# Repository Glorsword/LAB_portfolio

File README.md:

# LAB_portfolio
Here you would find sample projects from our team

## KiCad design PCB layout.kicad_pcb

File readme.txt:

This project is quite simple, and it was the start for our team, it almost had no challenges other than finding a suitable Battery, but I chose an unrealistic unpractical huge battery.
other than that I put this project just to rember our humble beginnings

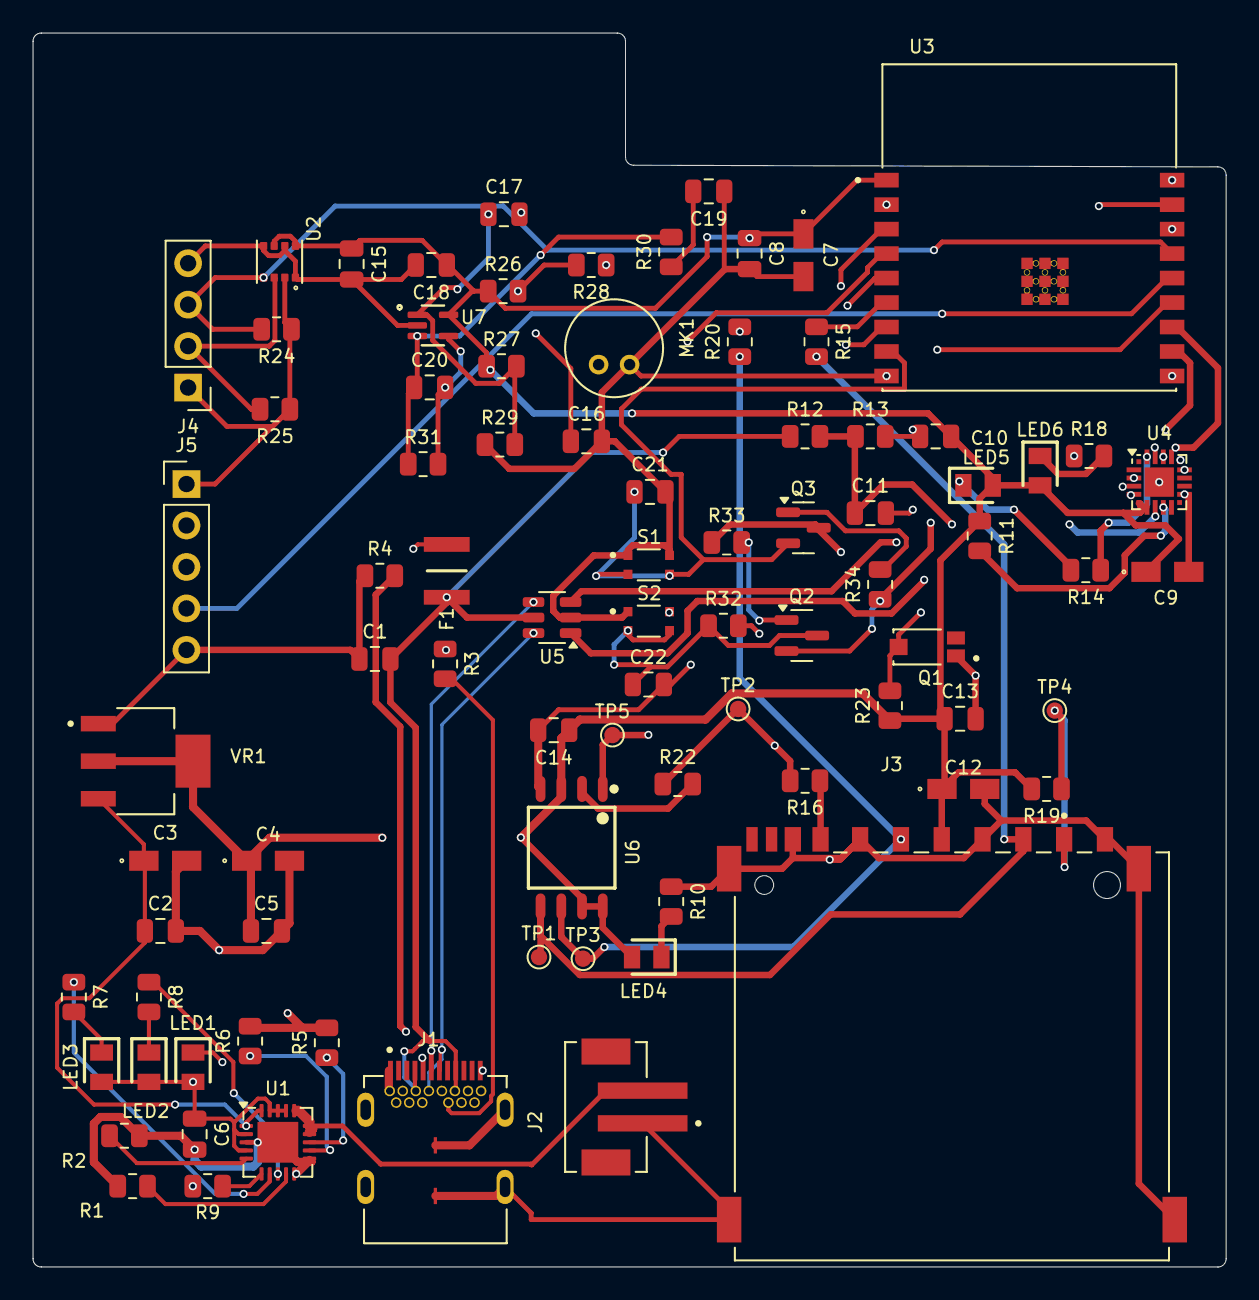
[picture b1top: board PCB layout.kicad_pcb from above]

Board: 4 copper layers, 73.1 x 75.6 mm, 85 parts (0 on the bottom side), 59 nets.

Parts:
C1, C2, C5, C8, C10, C13, C14, C15, C16, C18, C20, C21: 0.1u; C_0805_2012Metric
C3, C4, C7, C12: 10u; T491A
C6, C11, C19, C22: 1u; C_0805_2012Metric
C9: 4.7u; T491A
C17: 10n; C_0805_2012Metric
F1: 0ZCH0110AF2E; FUSC3226X100N
J1: SS-52400-002; BELFUSE_SS-52400-002
J2: B2B-PH-SM4-TB; JST_B2B-PH-SM4-TB
J3: GSD090012SEU; AMPHENOL_GSD090012SEU
J4: Conn_01x04_Pin; PinHeader_1x04_P2.54mm_Vertical
J5: Conn_01x05_Pin; PinHeader_1x05_P2.54mm_Vertical
LED1, LED4, LED5: LTST-C170KRKT; LEDC2012X120N
LED2, LED6: LTST-C170GKT; LEDC2012X120N
LED3: LTST-C170TBKT; LEDC2012X120N
MK1: CMC-5042PF-AC; CUI_CMC-5042PF-AC
Q1: TEMT6000X01; TRANS_TEMT6000X01
Q2, Q3: BC817; SOT-23
R1, R2, R19, R23, R30, R32, R33, R34: 10K; R_0805_2012Metric
R3, R4: 5.1K; R_0805_2012Metric
R5, R26, R28: 2K; R_0805_2012Metric
R6: 20K; R_0805_2012Metric
R7, R8, R9, R10, R14, R18: 470; R_0805_2012Metric
R11: 1K; R_0805_2012Metric
R12: 22.1K; R_0805_2012Metric
R13: 47.5K; R_0805_2012Metric
R15, R16, R20, R22: 50; R_0805_2012Metric
R24, R25: 4.7K; R_0805_2012Metric
R27, R29: 1M; R_0805_2012Metric
R31: 100K; R_0805_2012Metric
S1: BOOT; SW_USLPT2819DT2TR
S2: RESET; SW_USLPT2819DT2TR
TP1: TestMOSI; TestPoint_Pad_D1.0mm
TP2: TestMISO; TestPoint_Pad_D1.0mm
TP3: TestSCLK; TestPoint_Pad_D1.0mm
TP4: TestCS_SD; TestPoint_Pad_D1.0mm
TP5: TestCS; TestPoint_Pad_D1.0mm
U1: MCP73871; QFN-20-1EP_4x4mm_P0.5mm_EP2.5x2.5mm
U2: BME280; PSON65P250X250X100-8N
U3: ESP32-C3-WROOM-02-H4; MODULE_ESP32-C3-WROOM-02-H4
U4: CP2102N-Axx-xQFN20; SiliconLabs_QFN-20-1EP_3x3mm_P0.5mm_EP1.8x1.8mm
U5: USBLC6-2SC6; SOT-23-6
U6: W25Q32JVSSIQ; SOIC127P790X216-8N
U7: MAX4466EXK; SOT65P210X110-5N
VR1: LM1117MPX-3.3; VREG_LM1117MPX-3.3_NOPB

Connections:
3.3V: J4.1, J5.1, R24.1, R25.1, R32.2, U2.2 (CSB)
+3.3V: C4.1, C5.1, C7.1, C8.1, C9.1, C10.1, C12.1, C13.1, C14.1, C15.1, C18.1, J3.4 (VDD1), LED4.2 (A), LED5.2 (A), LED6.2 (A), R11.1, R19.2, R23.1, R26.1, R27.1, U2.6 (VDDIO), U2.8 (VDD), U3.1 (3V3), U4.6 (VDD), U4.7 (VREGIN), U6.3 (~WP(IO2)), U6.7 (~HOLD/~RESET(IO3)), U6.8 (VCC), U7.5 (VCC), VR1.2 (VOUT_2), VR1.4 (VOUT_4)
+5V: C2.1, C3.1, U1.1 (OUT), U1.20 (OUT), VR1.3 (VIN)
/+5V_USB: C6.1, F1.2, LED1.2 (A), LED2.2 (A), LED3.2 (A), U1.2 (VPCC), U1.4 (PROG2), U1.17 (CE), U1.18 (IN), U1.19 (IN)
/CHARGED: R8.1, U1.8 (STAT1/~LBO)
/CHARGED POWER IS GOOD: R7.1, U1.7 (STAT2)
/CHARGING: R9.1, U1.6 (~PG)
/ESP32-C3-02/BOOT: C21.1, Q3.2 (E), S1.3, S1.4, U3.8 (IO9)
/ESP32-C3-02/CS: TP5.1, U3.10 (IO10), U6.1 (~CS)
/ESP32-C3-02/CS_SD: J3.1 (CD/DAT3), R19.1, TP4.1, U3.18 (IO0)
/ESP32-C3-02/DTR: Q3.3 (C), R33.1, U4.15 (~CTS)
/ESP32-C3-02/EN: C22.1, Q2.3 (C), R32.1, S2.3, S2.4, U3.2 (EN)
/ESP32-C3-02/GPIO8: J5.2, U3.7 (IO8)
/ESP32-C3-02/GPIO18: J5.3, U3.13 (IO18)
/ESP32-C3-02/GPIO19: J5.4, U3.14 (IO19)
/ESP32-C3-02/MIC_OUT: C20.2, R31.2, U3.4 (IO5), U7.4 (OUT)
/ESP32-C3-02/MISO_DO: R16.2, R22.1, TP2.1, U3.16 (IO2)
/ESP32-C3-02/MOSI_DI: J3.2 (CMD), R15.2, TP1.1, U6.5 (DI(IO0))
/ESP32-C3-02/PHOTO_C: Q1.3, R23.2, U3.17 (IO1)
/ESP32-C3-02/RTS: Q2.2 (E), R34.1, U4.16 (~RTS)
/ESP32-C3-02/RX_TX: U3.12 (TXD), U4.17 (RXD)
/ESP32-C3-02/SCL: J4.3, R24.2, U2.4 (SCK), U3.15 (IO3)
/ESP32-C3-02/SCLK: J3.5 (CLK), R20.1, TP3.1, U6.6 (CLK)
/ESP32-C3-02/SDA: J4.2, R25.2, U2.3 (SDI), U3.3 (IO4)
/ESP32-C3-02/TX_RX: U3.11 (RXD), U4.18 (TXD)
/ESP32-C3-02/USB_D+: U4.4 (D+), U5.3 (I/O2)
/ESP32-C3-02/USB_D-: U4.5 (D-), U5.1 (I/O1)
/PWD_LED: LED4.1 (K), R10.2
/USB_DN: J1.A7 (DN1), J1.B7 (DN2), U5.6 (I/O1)
/USB_DP: J1.A6 (DP1), J1.B6 (DP2), U5.4 (I/O2)
/VBAT: J2.2, U1.14 (V_{BAT}), U1.15 (V_{BAT}), U1.16 (V_{BAT_SENSE})
/VBUS: C1.2, F1.1, J1.A4 (VBUSA1), J1.A9 (VBUSA2), J1.B4 (VBUSB1), J1.B9 (VBUSB2), R12.1, U5.5 (VBUS)
GND: C1.1, C2.2, C3.2, C4.2, C5.2, C6.2, C7.2, C8.2, C9.2, C10.2, C11.2, C12.2, C13.2, C14.2, C15.2, C16.2, C18.2, C19.1, C21.2, C22.2, J1.A1 (GNDA1), J1.A12 (GNDA2), J1.B1 (GNDB1), J1.B12 (GNDB2), J1.G1 (GND/SHIELD), J1.G2 (GND/SHIELD), J1.G3 (GND/SHIELD), J1.G4 (GND/SHIELD), J1.S1 (GND/SHIELD), J1.S2 (GND/SHIELD), J1.S3 (GND/SHIELD), J1.S4 (GND/SHIELD), J2.1, J3.3 (VSS1), J3.6 (VSS2), J3.8 (DAT1), J3.9 (DAT2), J3.G1 (SHIELD_GND), J3.G2 (SHIELD_GND), J3.G3 (SHIELD_GND), J3.G4 (SHIELD_GND), J4.4, J5.5, MK1.GND, Q1.1, R1.1, R2.1, R3.1, R4.1, R5.2, R6.2, R10.1, R13.2, R29.1, S1.1, S1.2, S2.1, S2.2, U1.3 (SEL), U1.10 (V_{SS}), U1.11 (V_{SS}), U1.21 (V_{SS}), U2.1 (GND), U2.5 (SDO), U2.7 (GND), U3.9 (GND), U3.19 (GND), U3.20 (GND), U3.21 (GND), U3.22 (GND), U3.23 (GND), U3.24 (GND), U3.25 (GND), U3.26 (GND), U3.27 (GND), U3.28 (GND), U3.29 (GND), U3.30 (GND), U3.31 (GND), U3.32 (GND), U3.33 (GND), U3.34 (GND), U3.35 (GND), U3.36 (GND), U3.37 (GND), U3.38 (GND), U3.39 (GND), U4.3 (GND), U4.12 (GND), U4.21 (GND), U5.2 (GND), U6.4 (GND), U7.2 (GND), VR1.1 (GND)
unnamed: C16.1, R26.2, R28.2
unnamed: C17.2, MK1.OUT, R28.1
unnamed: C19.2, R30.1
unnamed: J1.A5 (CC1), R4.2
unnamed: J1.B5 (CC2), R3.2
unnamed: J3.7 (DAT0), R16.1
unnamed: LED1.1 (K), R9.2
unnamed: LED2.1 (K), R8.2
unnamed: LED3.1 (K), R7.2
unnamed: LED5.1 (K), R14.2
unnamed: LED6.1 (K), R18.2
unnamed: Q2.1 (B), R33.2
unnamed: Q3.1 (B), R34.2
unnamed: R5.1, U1.13 (PROG1)
unnamed: R6.1, U1.12 (PROG3)
unnamed: R2.2, U1.5 (THERM)
unnamed: R1.2, U1.9 (~TE)
unnamed: R20.2, U3.5 (IO6)
unnamed: R15.1, U3.6 (IO7)
unnamed: C11.1, R12.2, R13.1, U4.8 (VBUS)
unnamed: R11.2, U4.9 (~RST)
unnamed: R18.1, U4.19 (~RXT/GPIO.3)
unnamed: R14.1, U4.20 (~TXT/GPIO.2)
unnamed: R22.2, U6.2 (DO(IO1))
unnamed: C17.1, R27.2, R29.2, U7.1 (IN+)
unnamed: C20.1, R30.2, R31.1, U7.3 (IN-)

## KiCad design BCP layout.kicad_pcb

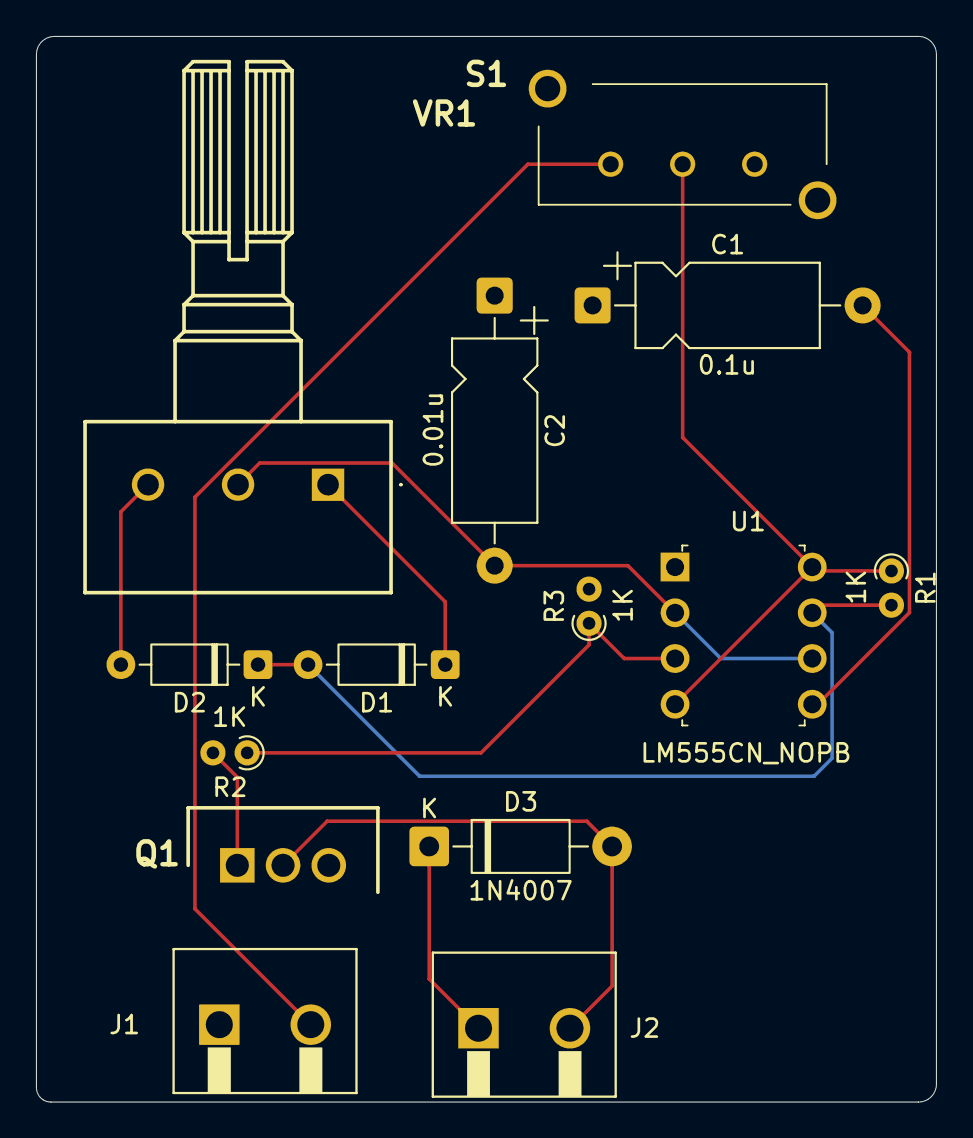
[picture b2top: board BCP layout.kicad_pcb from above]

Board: 2 copper layers, 50.0 x 59.2 mm, 14 parts (0 on the bottom side), 12 nets.

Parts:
C1: 0.1u; CP_Axial_L10.0mm_D4.5mm_P15.00mm_Horizontal
C2: 0.01u; CP_Axial_L10.0mm_D4.5mm_P15.00mm_Horizontal
D1, D2: 1N4148; D_DO-35_SOD27_P7.62mm_Horizontal
D3: 1N4007; D_DO-41_SOD81_P10.16mm_Horizontal
J1, J2: 1760510000; 1760490000
Q1: IRFZ24NPBF; TO254P469X1042X1967-3P
R1, R2, R3: 1K; R_Axial_DIN0204_L3.6mm_D1.6mm_P1.90mm_Vertical
S1: MHS12204
U1: LM555CN_NOPB; DIP-8_W7.62mm
VR1: P160KN2-0QC20B100K; P160KN20QC20B100K

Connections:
+12V: R1.1, S1.2, U1.4 (~RST), U1.8 (VDD)
GND: C1.1, C2.1, J1.1, Q1.3 (S), R3.2, U1.1 (GND)
unnamed: D1.2 (A), D2.1 (K), R1.2, U1.7 (DIS)
unnamed: D1.1 (K), VR1.1 (CCW)
unnamed: D2.2 (A), VR1.3 (CW)
unnamed: D3.2 (A), J2.2, Q1.2 (D)
unnamed: D3.1 (K), J2.1
unnamed: J1.2, S1.1
unnamed: Q1.1 (G), R2.2
unnamed: C1.2, U1.5 (CONT)
unnamed: R2.1, R3.1, U1.3 (OUT)
unnamed: C2.2, U1.2 (TRIG), U1.6 (THR), VR1.2 (WIPER)

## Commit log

2025-08-31 Create LED_torch schema
    installing the components
2025-08-31 Update LED_torch schema
    done the connections
2025-08-31 Update LED_torch schema
    Annotations and ERC run
2025-08-31 Update LED_torch schema
    added the footprints
2025-08-31 Create LED_torch
    components placement
2025-08-31 Update LED_torch
    Done with routing and erc is running good
2025-09-01 Create readme_solar
2025-09-01 Update readme_solar
2025-09-01 Rename image.png to 3D back.png
2025-09-01 Rename image.png to PCP layout.png
2025-09-01 Rename PCP layout.png to PCB layout.png
2025-09-01 Rename image.png to POM.png
2025-09-01 Rename image.png to Schematic.png
2025-09-01 Update readme_solar
    polishing
2025-09-01 Create readme_breadboard_power_supply
2025-09-01 Create Readme_MCU
2025-09-01 Update Readme_MCU
2025-09-01 Create Readme_motor
2025-09-01 Update Readme_motor
2025-09-01 Create Readme_Monitor
2025-09-01 Create readme_home
2025-09-01 Create Readme_IR
2025-09-01 Create readme_charger
2025-09-01 Create Readme_ESP32
2026-02-10 Add files via upload
    This is our documentation for designing a Configurable Vienna Rectifier for Power Electronics applications
2026-02-10 Add files via upload
    This is our documentation of a Configurable Swiss Rectifier for power electronics applications
